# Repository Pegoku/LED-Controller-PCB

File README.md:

# LED Controller
A simple monochromatic LED controller for Home Assistant, powered by ESPHome on a XIAO ESP32-C3.

## Features
- Brightness control via Home Assistant UI  
- Over-the-air (OTA) updates  

## Images
<details>
  <summary>Final project</summary>

</details>
<details>
  <summary>Schematic</summary>

</details>
<details>
  <summary>PCB</summary>

</details>

## BOM
| Item Name           | What the item is for in your project | Item source                                                                             | Item price     | Total Price     |
|---------------------|--------------------------------------|-----------------------------------------------------------------------------------------|----------------|-----------------|
| JST XH connector    | Light connector                      | https://es.aliexpress.com/item/10050074608978V65.html                                   | 1.22€          | 77.15€          |
| SS2040FL Diode      | Reverse polarity protection          | https://es.aliexpress.com/item/1005009042615388.html                                    | 5.39€          | 87.75 USD       |
| 5.5mm jack          | PSU connector                        | https://es.aliexpress.com/item/10000000716763.html                                      | 1.39€          |                 |
| BS170               | Driver for power mosfet              | https://es.aliexpress.com/item/1005007109406326.html                                    | 1.44€          |                 |
| IRLZ34N             | Power Mosfet                         | https://es.aliexpress.com/item/1005007174349301.html                                    | 1.90€          |                 |
| 220 Ω resistor      | Mosfet series resistor               | https://es.aliexpress.com/item/1005006750101049.html                                    | 1.08€          |                 |
| 10 kΩ resistor      | Pullup resistor                      | https://es.aliexpress.com/item/1005006750101049.html                                    | 1.08€          |                 |
| XIAO ESP32C3        | MCU                                  | https://es.aliexpress.com/item/1005006828136326.html                                    | 8.29€          |                 |
| L7805CV             | Regulate 5V                          | https://es.aliexpress.com/item/1005004989595789.html                                    | 1.69€          |                 |
| PCB                 | The main PCB                         | https://aisler.com/                                                                     | 35.67€         |                 |
| ELEGOO PLA filament | Printing case                        | https://www.amazon.es/-/en/Filament-Printer-Dimensional-Accuracy-Printers/dp/B0CD77VHBZ | 18€            |                 |

## Configuration

All firmware configuration lives in [code.yaml](code.yaml):

```yaml
esphome:
  name: led-controller
  friendly_name: LED-Controller

esp32:
  board: esp32-c3-devkitm-1
  framework:
    type: arduino

logger:

api:
  encryption:
    key: "YOUR_API_ENCRYPTION_KEY"

ota:
  - platform: esphome
    password: "YOUR_OTA_PASSWORD"

wifi:
  ssid: !secret wifi_ssid
  password: !secret wifi_password
  ap:
    ssid: "Led-Controller"
    password: "FALLBACK_AP_PASSWORD"

light:
  - platform: monochromatic
    name: "Light Bar"
    output: gpio_light
    id: light_bar1
    icon: "mdi:ceiling-light"

output:
  - platform: ledc
    pin: GPIO10
    id: gpio_light
    inverted: true

captive_portal:
```

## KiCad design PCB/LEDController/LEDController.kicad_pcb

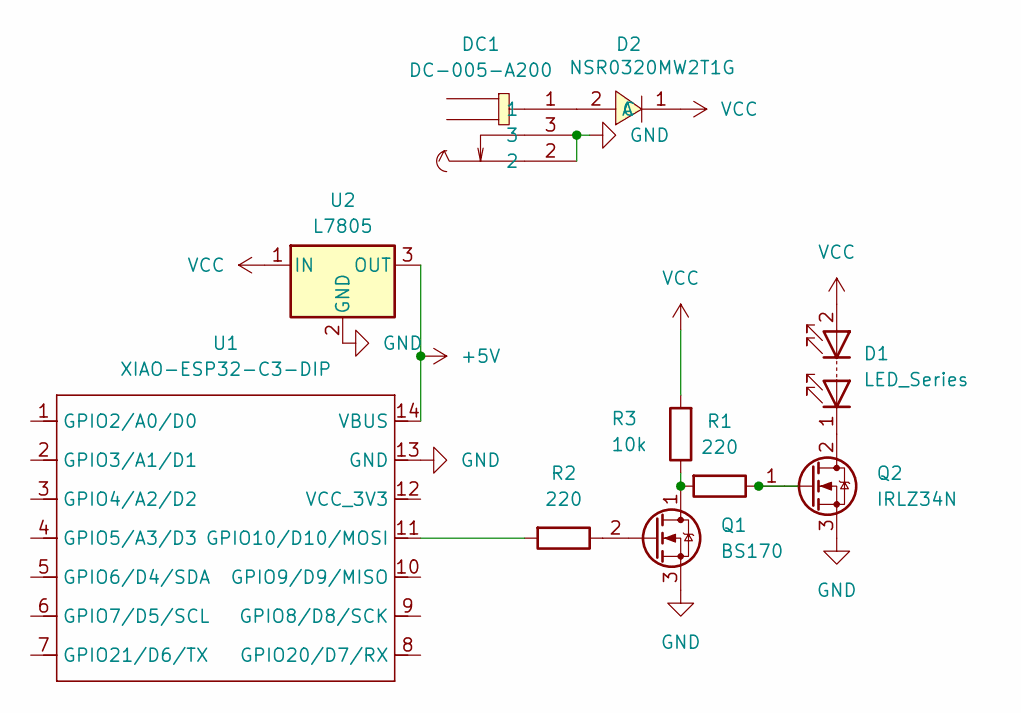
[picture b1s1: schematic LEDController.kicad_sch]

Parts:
D1: LED_Series; JST_XH_B2B-XH-AM_1x02_P2.50mm_Vertical
D2: NSR0320MW2T1G; SOD-323_L1.8-W1.3-LS2.5-RD; LCSC Part C48192
DC1: DC-005-A200; DC-IN-TH_DC-005-A200; LCSC Part C720557
Q1: BS170; TO-92_Inline
Q2: IRLZ34N; TO-220-3_Vertical
R1, R2: 220; R_Axial_DIN0309_L9.0mm_D3.2mm_P12.70mm_Horizontal
R3: 10k; R_Axial_DIN0309_L9.0mm_D3.2mm_P12.70mm_Horizontal
U1: XIAO-ESP32-C3-DIP; XIAO-ESP32C3-DIP
U2: L7805; TO-220-3_Vertical

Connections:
+5V: U1.14 (VBUS), U2.3 (OUT)
GND: DC1.2, DC1.3, Q1.3 (S), Q2.3 (S), U1.13 (GND), U2.2 (GND)
unnamed: D1.1 (K), Q2.2 (D)
unnamed: D2.2 (A), DC1.1
unnamed: Q1.1 (D), R1.2, R3.1
unnamed: Q1.2 (G), R2.1
unnamed: Q2.1 (G), R1.1
unnamed: R2.2, U1.11 (GPIO10/D10/MOSI)
VCC: D1.2 (A), D2.1 (C), R3.2, U2.1 (IN)

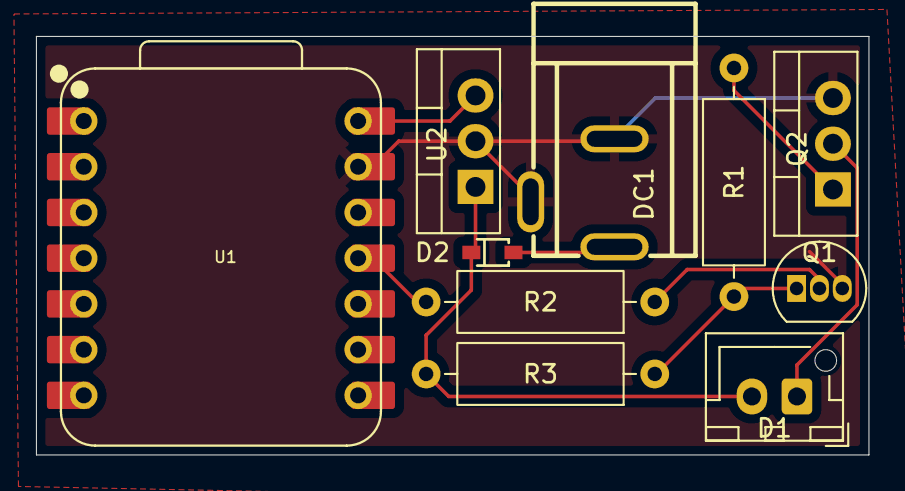
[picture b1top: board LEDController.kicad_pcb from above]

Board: 2 copper layers, 46.2 x 23.2 mm, 10 parts (0 on the bottom side), 9 nets.

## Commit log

2025-05-24 JOURNAL.md
2025-05-24 fix Journal
2025-05-24 README, BOM and images
2025-05-24 add PCB to BOM
2025-05-24 add items to BOM
2025-08-06 finish project
2025-08-06 Create LICENSE
